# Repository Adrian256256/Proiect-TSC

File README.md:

# E-Book Reader
## Project name: OpenBook  
**Author:** Teodor-Adrian Harea (333CA)  

---

## 1. Core Components  

### 1.1 Microcontroller: ESP32-C6  
| Specification          | Details                                                                 |
|------------------------|-------------------------------------------------------------------------|
| Architecture           | 32-bit RISC-V (Wi-Fi 6 802.11ax + Bluetooth 5)                         |
| Clock Speed            | Up to 160 MHz                                                          |
| Memory                 | 320 KB SRAM + 512 KB internal flash (expandable via external NOR flash)|
| Interfaces             | 30+ GPIO (SPI×2, I2C×1, UART×2, USB 2.0)                              |

---

## 2. Peripheral Modules  

### 2.1 E-Paper Display (Waveshare)  
- **Interface:** 4-wire SPI (MOSI/SCK/MISO/CS)  
- **Control Pins:**  
  - `EPD_RST` (Hardware reset)  
  - `EPD_DC` (Data/command selector)  
  - `EPD_BUSY` (Status monitoring)  
- **Power Characteristics:**  
  - 150 mA (active refresh)  
  - 0 mA (static display)  

### 2.2 Environmental Sensor (BME688)  
- **Measurements:** Temp/Humidity/Pressure/VOC  
- **Interface:** I2C (100-400 kHz)  
- **Accuracy:** ±0.5°C, ±3% RH  
- **Power:** 3.6 mA (active), 2.1 µA (sleep)  

### 2.3 Precision RTC (DS3231SN)  
- **Accuracy:** ±2ppm (±1 min/year)  
- **Features:**  
  - Battery backup (VBAT pin)  
  - Alarm interrupts (INT_RTC)  

### 2.4 Storage Solutions  
| Component       | Capacity | Interface | Speed           |
|-----------------|----------|-----------|-----------------|
| NOR Flash       | 64 MB    | QSPI      | 133 MHz         |
| microSD Slot    | Expandable | SPI      | 25 MHz          |

---

## 3. Power Management  

### 3.1 Power Architecture  
- **LiPo Charger:** MCP73831 (5V USB → 4.2V battery)  
- **Voltage Regulation:**  
  - XC6220A331MR-G (3.3V LDO)  
- **Battery Monitoring:** MAX17048G (I2C fuel gauge)  

### 3.2 Power States  
| Mode              | Current Draw | Runtime* |
|-------------------|--------------|----------|
| Active (measure + display) | 230 mA | 4h       |
| Deep Sleep (RTC only)      | 6 µA   | 1+ month |

*Assuming 1000mAh battery

---

## 4. Detailed Pin Configuration  

### 4.1 E-Paper Display Control  
| Pin Name      | Type    | Functionality                          | ESP32-C6 Connection |
|--------------|---------|----------------------------------------|---------------------|
| `EPD_RST`    | Output  | Hardware reset (active low)            | GPIO18              |
| `EPD_DC`     | Output  | Data/Command selection (SPI mode)      | GPIO21              |
| `EPD_BUSY`   | Input   | Busy status (high during refresh)      | GPIO19              |
| `EPD_CS`     | Output  | SPI chip select (active low)           | GPIO5               |
| `MOSI/SCK`   | SPI     | Main display data/clock lines          | SPI1_HOST           |

### 4.2 Storage Interfaces  
#### NOR Flash (W25Q512JVEIQ)  
| Pin         | Function                      | ESP32 Pin |
|-------------|-------------------------------|-----------|
| `FLASH_CS`  | QSPI chip select              | GPIO17    |
| `IO0-IO3`   | Quad SPI data lines           | QSPI bus  |

#### microSD Card Slot  
| Pin       | Function                | ESP32 Pin |
|-----------|-------------------------|-----------|
| `SS_SD`   | SPI slave select        | GPIO4     |
| `CD`      | Card detect (optional)  | GPIO22    |

### 4.3 System Management  
| Component    | Critical Pins               | Purpose                             |
|--------------|-----------------------------|-------------------------------------|
| **RTC**      | `SCL`/`SDA` (I2C)           | Timekeeping (DS3231SN)              |
|              | `INT_RTC`                   | Wake-up alarm interrupt             |
| **Power**    | `VBAT`                      | RTC backup battery (3V)             |
|              | `CHG_STAT`                  | LiPo charger status LED             |

### 4.4 User Interface  
| Pin       | Type      | Functionality                  |
|-----------|-----------|--------------------------------|
| `PAGE_UP` | GPIO      | Tactile button (internal pullup)|
| `PAGE_DN` | GPIO      | With debounce circuit          |
| `PWR_HLD` | Output    | Maintains power when pressed   |

### 4.5 Debug Interfaces  
| Interface | Pins Used          | Baud Rate |
|-----------|--------------------|-----------|
| USB-C     | `DP`/`DM`          | 12 Mbps   |
| UART0     | `TX0`/`RX0`        | 115200    |

---

## 5. Optimization Strategies  

### 5.1 Low-Power Techniques  
- Dynamic clock scaling (160 MHz → 10 MHz when idle)  
- Peripheral power gating (MOSFET control for EPD/sensors)  
- SPI/I2C bus deactivation between transactions  

### 5.2 Data Logging Workflow  
1. Wake from deep sleep (RTC/alarm)  
2. Power sensors via GPIO  
3. Acquire measurements (BME688)  
4. Store to flash/SD  
5. Update EPD if threshold exceeded  
6. Return to deep sleep

### **Bill of Materials (BOM)**

| Category            | Component               | Description                          | Mouser Link | Datasheet Link |
|---------------------|-------------------------|--------------------------------------|-------------|----------------|
| **Microcontrollers & Modules** | ESP32-C6-WROOM-1-N8 | WiFi/Bluetooth Module | [Link](https://ro.mouser.com/ProductDetail/Espressif-Systems/ESP32-C6-WROOM-1-N8?qs=8Wlm6%252BaMh8ST02Gmwp74cw%3D%3D) | [Datasheet](https://ro.mouser.com/datasheet/2/891/Espressif_ESP32_C6_WROOM_1__Datasheet_V0_1_PRELIMI-3239987.pdf) |
| | W25Q512JVEIQ | 64MB External NOR Flash | [Link](https://ro.mouser.com/ProductDetail/Winbond/W25Q512JVEIQ?qs=l7cgNqFNU1jw6svr3at6tA%3D%3D) | [Datasheet](https://ro.mouser.com/datasheet/2/949/Winbond_W25Q512JV_Datasheet-3240039.pdf) |
| **Sensors** | BME688 | Environmental Sensor | [Link](https://ro.mouser.com/ProductDetail/Bosch-Sensortec/Evaluation-Kit-Board-BME688?qs=QNEnbhJQKvZD%2Fs%2Ff0WWu0Q%3D%3D) | [Datasheet](https://ro.mouser.com/datasheet/2/783/Bosch_sensortec_bme688_development_kit_flyer-3000177.pdf) |
| | DS3231SN# | RTC Module | [Link](https://ro.mouser.com/ProductDetail/Analog-Devices-Maxim-Integrated/DS3231SN?qs=1eQvB6Dk1vhUlr8%2FOrV0Fw%3D%3D) | [Datasheet](https://ro.mouser.com/datasheet/2/609/DS3231-3421123.pdf) |
| **Power Management** | MAX17048G+T10 | Battery Fuel Gauge | [Link](https://eu.mouser.com/ProductDetail/Analog-Devices-Maxim-Integrated/MAX17048G+T10?qs=D7PJwyCwLAoGnnn8jEPRBQ%3D%3D&srsltid=AfmBOoq0Uf9CVLtvuYCdL-b56-Pbwotx2XvoNmNfB9vf0O63iEPsWucA) | [Datasheet](https://eu.mouser.com/datasheet/2/609/MAX17048_MAX17049-3469099.pdf) |
| | MCP73831 | Li-Po Battery Charger | [Link](https://ro.mouser.com/ProductDetail/Microchip-Technology/MCP73831-2DCI-MC?qs=hH%252BOa0VZEiBQ%2FrptDRXKdg%3D%3D) | [Datasheet](https://ro.mouser.com/datasheet/2/268/MCP73831_Family_Data_Sheet_DS20001984H-3441711.pdf) |
| | XC6220A331MR-G | LDO Voltage Regulator 3.3V | [Link](https://ro.mouser.com/ProductDetail/Torex-Semiconductor/XC6220A331MR-G?qs=AsjdqWjXhJ8ZSWznL1J0gg%3D%3D) | [Datasheet](https://ro.mouser.com/datasheet/2/760/xc6220-3371556.pdf) |
| **Connectors & Protection** | USBLC6-2SC6Y | USB ESD Protection | [Link](https://eu.mouser.com/ProductDetail/STMicroelectronics/USBLC6-2SC6Y?qs=gNDSiZmRJS%2FOgDexvXkdow%3D%3D&srsltid=AfmBOooGFMy49XJWMdHSBGK6U_FDXdeHD6KsINSiWZt-au9axwzb1pgh) | [Datasheet](https://ro.mouser.com/datasheet/2/389/usblc6_2sc6y-1852505.pdf) |
| | FH34SRJ-24S-0.5SH | 24-pin Connector | [Link](https://ro.mouser.com/ProductDetail/Hirose-Connector/FH34SRJ-24S-0.5SH50?qs=iyLo5FA4poC8fzWlavnA7A%3D%3D) | [Datasheet](https://ro.mouser.com/datasheet/2/185/FH34SRJ_24S_0_5SH_50__CL0580_1255_6_50_2DDrawing_0-1615030.pdf) |
| **Passive Components** | SD0805S020S1R0 | 68μH Inductor | [Link](https://ro.mouser.com/ProductDetail/KYOCERA-AVX/SD0805S020S1R0?qs=jCA%252BPfw4LHbpkAoSnwrdjw%3D%3D) | [Datasheet](https://ro.mouser.com/datasheet/2/40/schottky-3165252.pdf) |
| | MBR0530 | Schottky Diode | [Link](https://ro.mouser.com/ProductDetail/onsemi-Fairchild/MBR0530?qs=VOMQJJE%252BBNniwJKcE3T43Q%3D%3D&srsltid=AfmBOorGETz4X7561cljdZB-BtAN4aC8w0OtRadqMgVwKqojAjDrxsqV) | [Datasheet](https://ro.mouser.com/datasheet/2/308/MBR0530_D-1810985.pdf) |

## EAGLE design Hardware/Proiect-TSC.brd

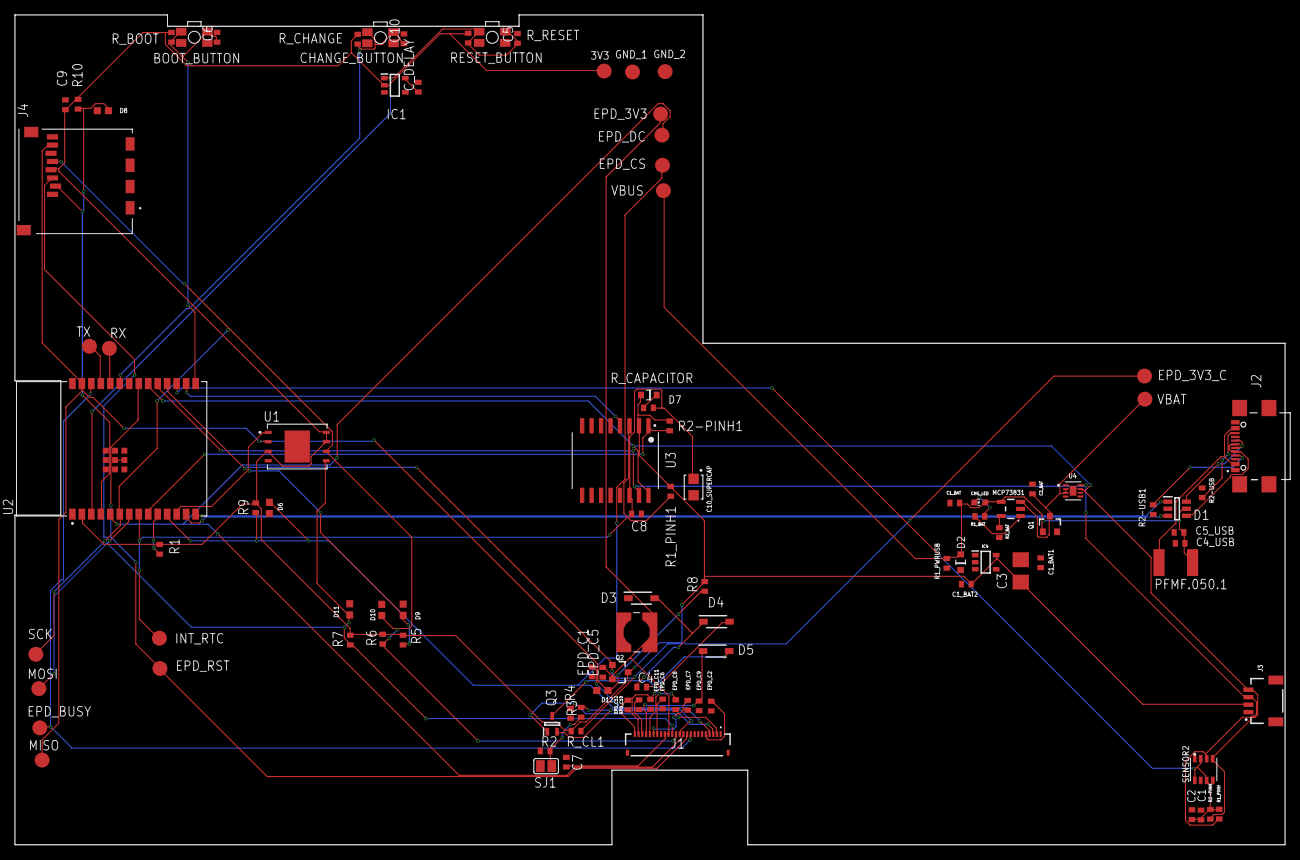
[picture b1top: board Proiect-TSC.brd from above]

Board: 2 copper layers, 170.2 x 111.2 mm, 103 parts (0 on the bottom side), 54 nets.

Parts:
3V3: TPTP20R; TP20R
BOOT_BUTTON: BUTTON_CUSYOMV1; MYBUTTON
C1, C2, C4_USB, C6, C8, C9, C10: 100nF; EAGLE-LTSPICE_C0402
C1_BAT, C1_BAT1, C1_BAT2, C2_BAT, C5_USB: 4.7uF; EAGLE-LTSPICE_C0402
C3: 100uF TANT; RCL_CT3528
C4: 4.7uF/25V; EAGLE-LTSPICE_C0402
C5: 1uF; EAGLE-LTSPICE_C0402
C7: 10uF; EAGLE-LTSPICE_C0402
C10_SUPERCAP: CPH3225A; CAPCP3225X100N
CHANGE_BUTTON: BUTTON_CUSYOMV1; MYBUTTON
CHG_LED: 1; ADAFRUIT_CHIP-LED0603
C_DELAY: 100nF; EAGLE-LTSPICE_C0402
D1: USBLC6-2SC6Y; SOT95P280X145-6N
D2, D7: ESP32_WROVER_AVX---SD0805S020S1R0_AVX_SD0805S020S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; ESP32_WROVER_AVX---SD0805S020S1R0_AVX_SD0805S020S1R0_0
D3, D4, D5: MBR0530; SOD3716X135N
D6, D8, D9, D10, D11, D12: PGB1010603MR; DIOC1608X36N
EPD_3V3, EPD_3V3_C: TPTP20R; TP20R
EPD_BUSY: TPTP20R; TP20R
EPD_C1, EPD_C2, EPD_C6, EPD_C7, EPD_C8, EPD_C9, EPD_C10, EPD_C11, EPD_C12: 1uF/50V; EAGLE-LTSPICE_C0402
EPD_C5: 0.1uF/50V; EAGLE-LTSPICE_C0402
EPD_CS: TPTP20R; TP20R
EPD_DC: TPTP20R; TP20R
EPD_RST: TPTP20R; TP20R
GND_1, GND_2: TPTP20R; TP20R
IC1: BD5229G-TR; SOT95P280X125-5N
IC4: XC6220A331MR-G; SOT95P280X120-5N
INT_RTC: TPTP20R; TP20R
J1: FH34SRJ-24S-0.5SH_99_; FH34SRJ24S05SH99
J2: SAMACSYS_PARTS_USB4110-GF-A; SAMACSYS_PARTS_USB4110GFA
J3: QWIIC_RIGHT_ANGLE; JST04_1MM_RA
J4: 112A-TAAR-R03_ATTEND; 112ATAARR03ATTEND
L1: 68uH; IND_4828-WE-TPC_WRE
MCP73831: ESP32_WROVER_SPARKFUN-IC-POWER_MCP73831; ESP32_WROVER_SPARKFUN-IC-POWER_SOT23-5
MISO: TPTP20R; TP20R
MOSI: TPTP20R; TP20R
PFMF.050.1: ESP32C6_VARISTORCN1812; ESP32C6_VARISTOR_CT/CN1812
Q1, Q2: 20V/4.2A/52mΩ/1.4W; ESP32_WROVER_SPARKFUN-DISCRETESEMI_SOT23-3
Q3: SI1308EDL-T1-GE3; SOT65P210X110-3N
R1, R1_PINH, R1_PINH1, R2-PINH, R2-PINH1, R4, R5, R6, R7, R8, R9, R10: 10K; ESP32_WROVER_EAGLE-LTSPICE_R0402
R1_BAT: 200; ESP32_WROVER_EAGLE-LTSPICE_R0402
R1_PWRUSB: 100K; ESP32_WROVER_EAGLE-LTSPICE_R0402
R2: 2.2; ESP32_WROVER_EAGLE-LTSPICE_R0402
R2-USB, R2-USB1: 5k1; ESP32_WROVER_EAGLE-LTSPICE_R0402
R2_BAT: 2K; ESP32_WROVER_EAGLE-LTSPICE_R0402
R3: 0.47; ESP32_WROVER_EAGLE-LTSPICE_R0402
RESET_BUTTON: BUTTON_CUSYOMV1; MYBUTTON
RX: TPTP20R; TP20R
R_BOOT: 10K; ESP32_WROVER_EAGLE-LTSPICE_R0402
R_CAPACITOR: 15; ESP32_WROVER_EAGLE-LTSPICE_R0402
R_CHANGE: 10K; ESP32_WROVER_EAGLE-LTSPICE_R0402
R_CL1: 10K; ESP32_WROVER_EAGLE-LTSPICE_R0402
R_RESET: 10K; ESP32_WROVER_EAGLE-LTSPICE_R0402
SCK: TPTP20R; TP20R
SENSOR2: ESP32_WROVER_BME680_BME680; ESP32_WROVER_BME680_PSON80P300X300X100-8N
SJ1: 1; SJ
TX: TPTP20R; TP20R
U1: W25Q512JVEIQ; SON127P600X800X80-9N
U2: ESP32-C6-WROOM-1-N8; XCVR_ESP32-C6-WROOM-1-N8
U3: DS3231SN#; SOIC127P1032X265-16N
U4: MAX17048G+T10; SON50P200X200X80-9N
VBAT: TPTP20R; TP20R
VBUS: TPTP20R; TP20R

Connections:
3V3: 3V3.TP, C1_BAT2.1, C3.+, C9.1, D7.2, IC1.2, IC4.5, J3.2, J4.P4, Q2.3, R1.2, R1_PINH1.2, R2-PINH1.2, R5.2, R6.2, R7.2, R8.2, R9.2, R10.2, R_BOOT.2, R_CHANGE.2, R_CL1.2, R_RESET.2, U1.3, U1.7, U1.8, U2.2, U3.2
32KHZ: R2-PINH1.1, U2.9, U3.1
DN: D1.4, J2.A7, J2.B7
DP: D1.6, J2.A6, J2.B6
EPD_3V3: C7.1, EPD_3V3.TP, EPD_C5.2, J1.15, J1.16, L1.2, Q2.2
EPD_3V3_C: EPD_3V3_C.TP, Q2.1, R_CL1.1, U2.18
EPD_BUSY: EPD_BUSY.TP, J1.9, U2.26
EPD_CS: D6.1, EPD_CS.TP, J1.12, R9.1, U2.11
EPD_DC: EPD_DC.TP, J1.11, U2.5
EPD_RST: EPD_RST.TP, J1.10, U2.21
FLASH_CS: D9.1, R5.1, U1.1, U2.12
GDR: J1.2, Q3.1, R4.2
GND: BOOT_BUTTON.2, C1.2, C1_BAT.2, C1_BAT1.1, C1_BAT1.2, C1_BAT2.2, C2.2, C2_BAT.2, C3.-, C4_USB.2, C5.2, C5_USB.2, C6.2, C7.2, C8.2, C9.2, C10.2, C10_SUPERCAP.2, CHANGE_BUTTON.2, C_DELAY.2, D1.2, D2.1, D3.1, D6.2, D8.2, D9.2, D10.2, D11.2, D12.2, EPD_C1.1, EPD_C2.1, EPD_C5.1, EPD_C6.1, EPD_C7.1, EPD_C8.1, EPD_C9.1, EPD_C10.1, EPD_C11.1, EPD_C12.1, GND_1.TP, GND_2.TP, IC1.3, IC4.1, IC4.2, IC4.3, J1.8, J1.17, J1.MP1, J1.MP2, J2.A1, J2.A12, J2.B1, J2.B12, J2.MP1, J2.MP2, J2.MP3, J2.MP4, J3.1, J4.G1, J4.G2, J4.G3, J4.G4, J4.P6, MCP73831.2, Q1.2, R1_PWRUSB.1, R2.1, R2-USB.2, R2-USB1.1, R2_BAT.1, R4.1, RESET_BUTTON.2, SENSOR2.1, SENSOR2.5, SENSOR2.7, SJ1.1, U1.4, U1.9, U2.1, U2.28, U2.29_1, U2.29_2, U2.29_3, U2.29_4, U2.29_5, U2.29_6, U2.29_7, U2.29_8, U2.29_9, U3.13, U4.1, U4.4, U4.6, U4.9
GPIO8: R1.1, U2.10
I2C_PW: C1.1, C2.1, R1_PINH.2, R2-PINH.2, SENSOR2.2, SENSOR2.6, SENSOR2.8, U2.17
INT_RTC: INT_RTC.TP, R1_PINH1.1, U2.8, U3.3
IO/BOOT: BOOT_BUTTON.3, BOOT_BUTTON.4, C6.1, R_BOOT.1, U2.15
IO/CHANGE: C10.1, CHANGE_BUTTON.3, CHANGE_BUTTON.4, R_CHANGE.1, U2.23
MISO: D12.1, J4.P7, MISO.TP, R8.1, U1.2, U2.27
MOSI: D11.1, J1.14, J4.P3, MOSI.TP, R7.1, U1.5, U2.7
unnamed: J2.A5, R2-USB1.2
unnamed: C_DELAY.1, IC1.5
unnamed: CHG_LED.C, R1_BAT.1
unnamed: C4.1, D3.2, D4.1
unnamed: MCP73831.1, R1_BAT.2
unnamed: D7.1, R_CAPACITOR.1
unnamed: MCP73831.5, R2_BAT.2
unnamed: J2.B5, R2-USB.1
unnamed: EPD_C12.2, J1.24
unnamed: EPD_C1.2, J1.4
unnamed: EPD_C2.2, J1.5
unnamed: EPD_C6.2, J1.18
unnamed: EPD_C7.2, J1.19
unnamed: EPD_C8.2, J1.20
unnamed: EPD_C10.2, J1.22
PREVGH: D5.1, EPD_C9.2, J1.21
PREVGL: D4.2, EPD_C11.2, J1.23
RESE: J1.3, Q3.2, R3.2
RESE': R2.2, R3.1, SJ1.2
RESET: C5.1, IC1.1, RESET_BUTTON.3, RESET_BUTTON.4, R_RESET.1, U2.3
RTC_RST: U2.16, U3.4
RX: RX.TP, U2.24
SCK: D10.1, J1.13, J4.P5, R6.1, SCK.TP, U1.6, U2.6
SCL: J3.4, R2-PINH.1, SENSOR2.4, U2.20, U3.16, U4.7
SDA: J3.3, R1_PINH.1, SENSOR2.3, U2.19, U3.15, U4.8
SRC: C4.2, D5.2, L1.1, Q3.3
SS_SD: D8.1, J4.P2, R10.1, U2.4
TX: TX.TP, U2.25
USB_D+: D1.1, U2.14
USB_D-: D1.3, U2.13
VBAT: C2_BAT.1, MCP73831.3, Q1.3, U4.2, U4.3, VBAT.TP
VBUS: C1_BAT.1, C4_USB.1, C5_USB.1, CHG_LED.A, D1.5, D2.2, MCP73831.4, PFMF.050.1.2, Q1.1, R1_PWRUSB.2, VBUS.TP
VRTC: C8.1, C10_SUPERCAP.1, R_CAPACITOR.2, U3.14
VUSB: J2.A4, J2.A9, J2.B4, J2.B9, PFMF.050.1.1

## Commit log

2025-04-14 Create LICENSE

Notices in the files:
parts and their libraries:
COPYRIGHT: Copyright (C) 2024 Ultra Librarian. All rights reserved.
